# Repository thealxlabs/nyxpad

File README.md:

# ⬡ Nyx Pad

<div align="center">

**Every developer's macropad. Powered by [Conductor](https://github.com/thealxlabs/conductor) AI.**

*by Alexander Wondwossen ([@thealxlabs](https://github.com/thealxlabs)) — Grade 7, Toronto 🇨🇦*

</div>

---

## What is Nyx Pad?

Nyx Pad is a custom 6-key macropad — think DIY Stream Deck — that talks to **Conductor**, my own AI integration CLI. Press a key and Nyx (the [LocalCode](https://github.com/TheLocalCodeTeam/localcode) mascot) animates on the OLED while Conductor fetches weather, crypto prices, GitHub stats, and more.

**3 profiles · hold actions · Pomodoro timer · screensaver · boot greeting**

Built on a Seeed XIAO RP2040 with KMK firmware. Designed from scratch for Hack Club Blueprint. Cost to me: $0.

---

## Features

### Stream Deck style OLED
128×32 OLED shows Nyx as a pixel art character reacting to every keypress. Status bar shows profile and key hints.

### 3 Profiles (encoder hold to switch)
| Profile | Keys |
|---------|------|
| **CODE** `</>` | GitHub, system stats, translate, weather, crypto, jokes |
| **CHILL** `uwu` | Music, weather, jokes, quotes, trivia, vibes |
| **MEET** `cam` | Mute, timer, focus, lock, notes, done |

### Key hold (2 seconds)
Every key has a secondary action on hold. K1 hold always starts a **Pomodoro timer**.

### Encoder
- Rotate = volume
- Click = mute
- Hold = switch profile

### Screensaver (30s idle)
Nyx cycles through: batting a hexagon around → getting tired → falling asleep with ZZZs → waking back up.

### Boot greeting
On plug-in, Nyx wakes up with an animation and says *"hey alex!"*

---

## Hardware

| Part | Qty |
|------|-----|
| Seeed XIAO RP2040 | 1 |
| Cherry MX Switches | 6 |
| MX Keycaps 1U | 6 |
| SSD1306 OLED 128×32 (0.91") | 1 |
| EC11 Rotary Encoder | 1 |
| 4.7kΩ Resistor 0402 | 2 |
| 100nF Capacitor 0402 | 1 |
| Custom PCB 80×70mm 2-layer | 1 |
| 3D Printed Case | 1 set |
| M2.5 Screws 6mm | 4 |

---

## Pin Map

| Signal | XIAO Pin |
|--------|----------|
| K1–K6 | D0–D5 |
| OLED SDA | D6 |
| OLED SCL | D7 |
| Encoder CLK | D8 |
| Encoder DT | D9 |
| Encoder SW | D10 |

---

## Setup

### 1. Flash CircuitPython
Hold BOOT on XIAO while plugging in. Copy [CircuitPython 9.x for XIAO RP2040](https://circuitpython.org/board/seeeduino_xiao_rp2040/) `.uf2` onto the `RPI-RP2` drive.

### 2. Install libraries
Copy to `lib/` on CIRCUITPY:
- `kmk/` from [KMKfw/kmk_firmware](https://github.com/KMKfw/kmk_firmware)
- `adafruit_displayio_ssd1306.mpy`
- `adafruit_display_text/`

### 3. Flash firmware
Copy `Firmware/main.py` to root of CIRCUITPY drive.

### 4. Install Conductor
```bash
curl -fsSL https://raw.githubusercontent.com/thealxlabs/conductor/main/install.sh | bash
conductor ai setup
```

### 5. Run the bridge
```bash
pip install pyserial plyer
python Firmware/bridge.py
```

---

## How it works

```
Key press → KMK sends F-key via USB HID
          → bridge.py reads serial signal
          → calls conductor CLI command
          → result shown as desktop notification
          → OLED shows Nyx reaction
```

---

## Project Structure

```
nyxpad/
├── PCB/                  KiCAD source files
├── CAD/                  OpenSCAD case
├── Firmware/
│   ├── main.py           KMK firmware (drop onto XIAO)
│   └── bridge.py         PC-side Conductor bridge
├── production/           Gerbers, STLs, compiled firmware
├── BOM.csv               Bill of materials
└── README.md
```

---

## Related

- [Conductor](https://github.com/thealxlabs/conductor) — AI CLI powering the keys
- [LocalCode](https://github.com/TheLocalCodeTeam/localcode) — Nyx's home
- [KMK Firmware](https://github.com/KMKfw/kmk_firmware) — keyboard firmware

---

<div align="center">
Made with ❤️ in Toronto for <a href="https://hackclub.com/blueprint">Hack Club Blueprint</a>
</div>

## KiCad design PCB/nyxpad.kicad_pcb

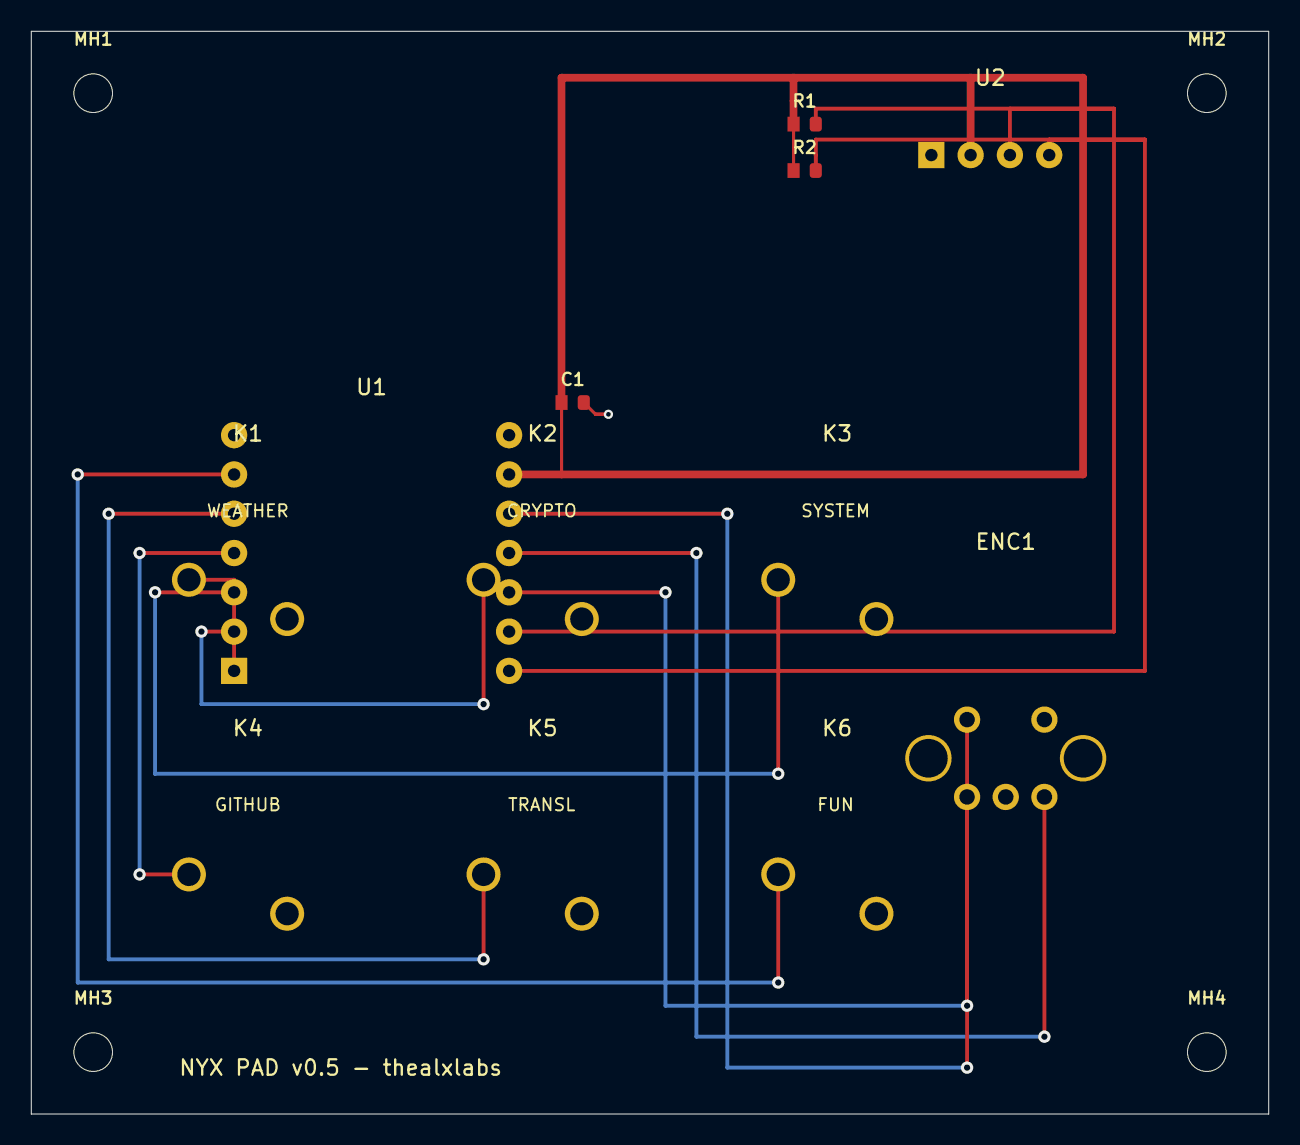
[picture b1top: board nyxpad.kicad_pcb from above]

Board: 2 copper layers, 80.0 x 70.0 mm, 16 parts (0 on the bottom side), 13 nets.

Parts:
C1: 100nF; C_0402_1005Metric
ENC1: EC11; RotaryEncoder_Alps_EC11E-Switch_Vertical_H20mm
K1, K2, K3, K4, K5, K6: SW_MX; MX-1U-PCB
MH1, MH2, MH3, MH4: MountingHole_2.5mm
R1, R2: 4.7k; R_0402_1005Metric
U1: XIAO-RP2040; PinHeader_2x07_P2.54mm_Vertical
U2: OLED-SSD1306; PinHeader_1x04_P2.54mm_Vertical

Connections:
3V3: C1.1, R1.1, R2.1, U1.3V3, U2.2
ENC_A: ENC1.A, U1.D8
ENC_B: ENC1.B, U1.D9
ENC_SW: ENC1.SW1, U1.D10
GND: C1.2, ENC1.C, ENC1.SW2, K1.2, K2.2, K3.2, K4.2, K5.2, K6.2, U1.GND_L, U1.GND_R, U2.1
K1_NET: K1.1, U1.D0
K2_NET: K2.1, U1.D1
K3_NET: K3.1, U1.D2
K4_NET: K4.1, U1.D3
K5_NET: K5.1, U1.D4
K6_NET: K6.1, U1.D5
SCL: R1.2, U1.D7, U2.3
SDA: R2.2, U1.D6, U2.4

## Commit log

2026-03-18 initial commit - nyxpad v1
2026-03-18 initial commit — nyx pad v1

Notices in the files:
README.md:
License: MIT
